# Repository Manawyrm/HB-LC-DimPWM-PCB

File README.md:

HomeBrew 16 channel dimmer
==========================

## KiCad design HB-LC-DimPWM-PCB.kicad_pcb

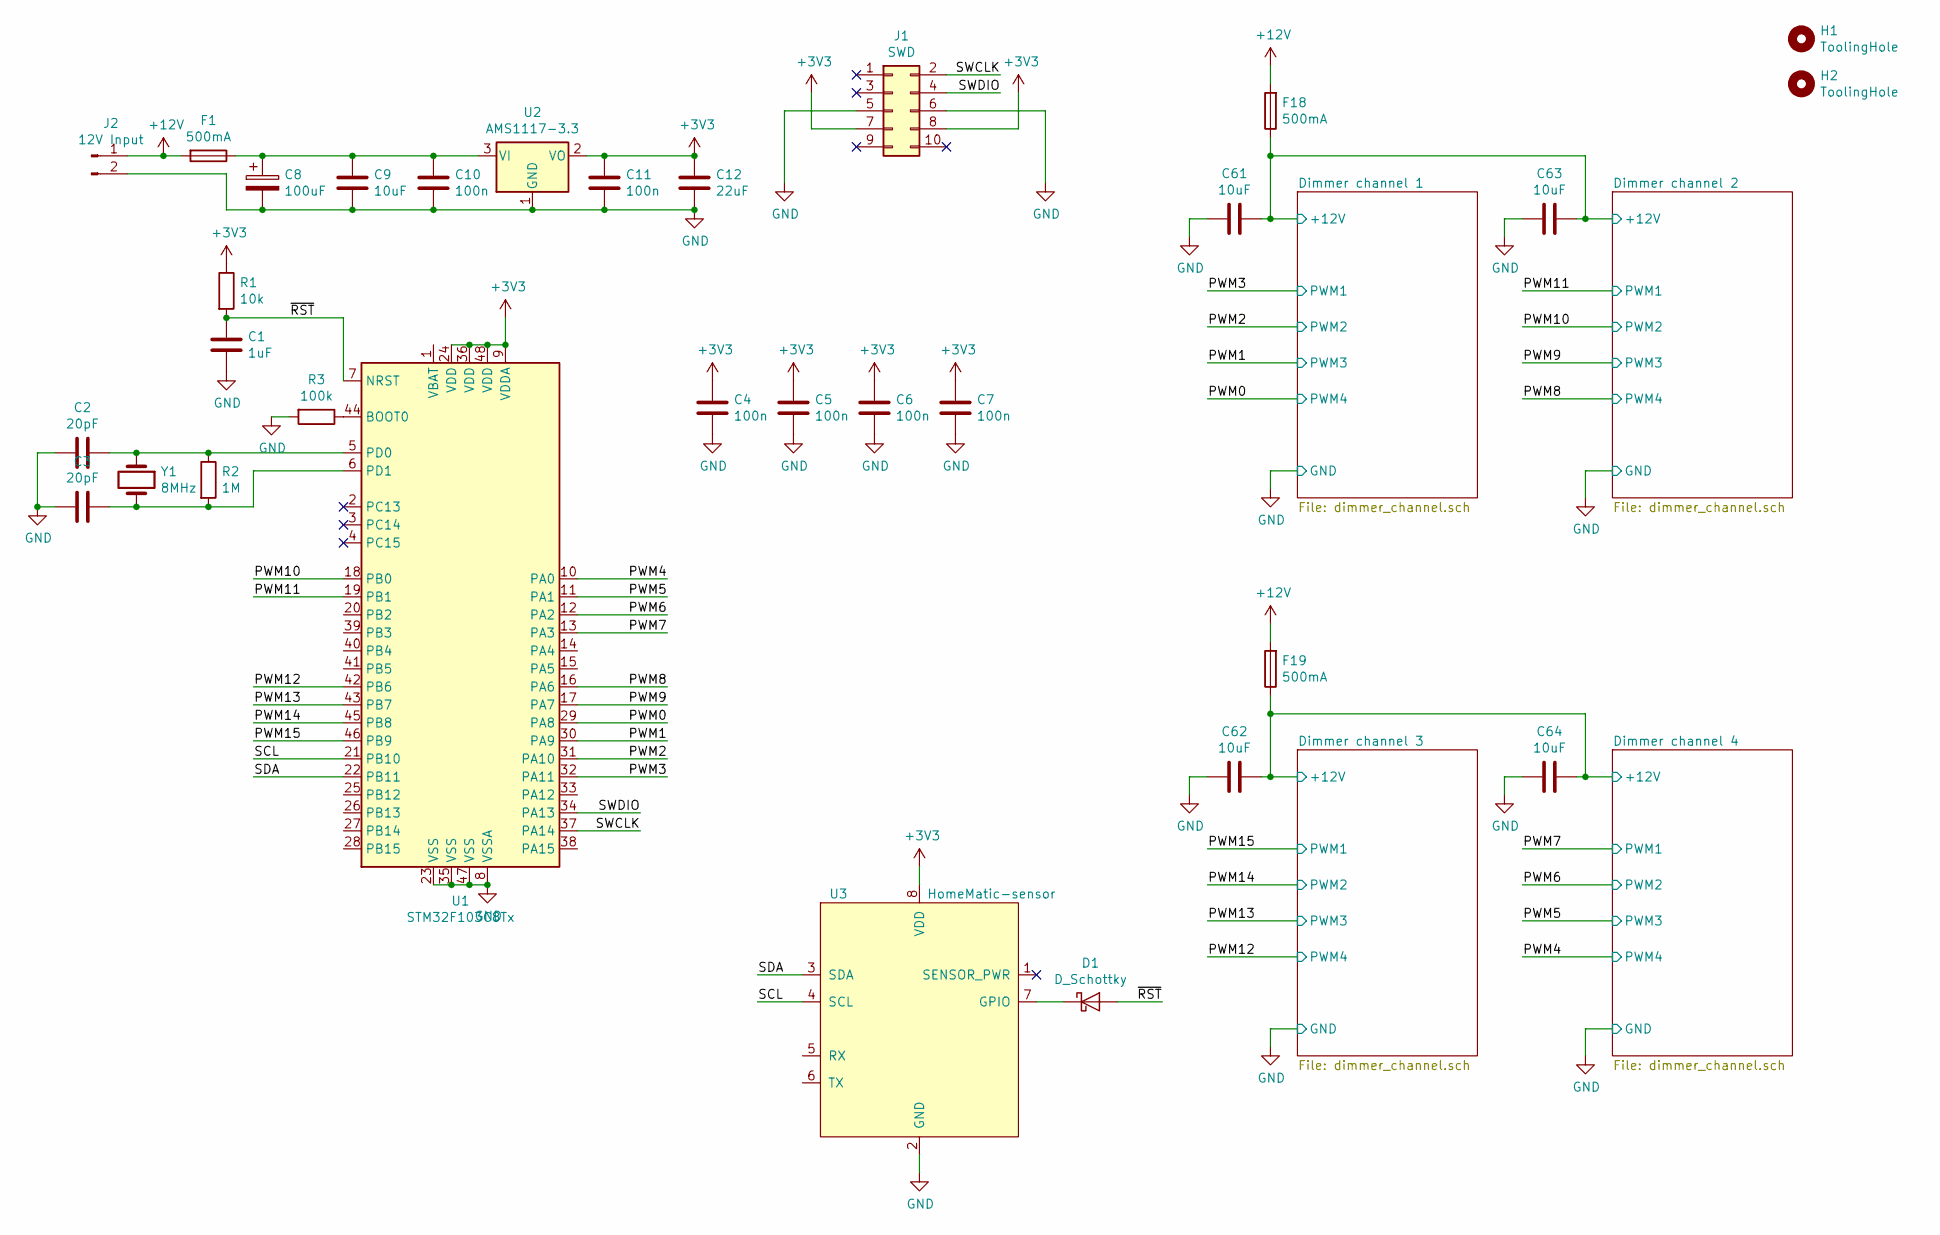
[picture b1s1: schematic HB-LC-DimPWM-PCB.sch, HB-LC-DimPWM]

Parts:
C1: 1uF; C_0402_1005Metric; LCSC C52923
C2, C3: 20pF; C_0402_1005Metric; LCSC C1554
C4, C5, C6, C7, C10, C11: 100n; C_0603_1608Metric; LCSC C14663
C8: 100uF; CP_Elec_8x6.7; LCSC C127967
C9: 10uF; C_0805_2012Metric; LCSC C15850
C12: 22uF; C_0603_1608Metric; LCSC C59461
C61, C62, C63, C64: 10uF; C_1206_3216Metric; LCSC C13585
D1: D_Schottky; D_SOD-123; LCSC C8598
F1, F18, F19: 500mA; Fuse_2512_6332Metric; LCSC C312001
H1, H2: ToolingHole; ToolingHole_JLCSMT
J1: SWD; IDC-Header_2x05_P2.54mm_Vertical
J2: 12V Input; Wago_714-162_1x02_P3.50mm_Horizontal
R1: 10k; R_0402_1005Metric; LCSC C25744
R2: 1M; R_0402_1005Metric; LCSC C26083
R3: 100k; R_0402_1005Metric; LCSC C25741
U1: STM32F103C8Tx; LQFP-48_7x7mm_P0.5mm; LCSC C8734
U2: AMS1117-3.3; SOT-223-3_TabPin2; LCSC C6186
U3: HomeMatic-sensor
Y1: 8MHz; Crystal_SMD_5032-2Pin_5.0x3.2mm; LCSC C115962

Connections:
+3V3: C4.1, C5.1, C6.1, C7.1, C11.1, C12.1, J1.7, J1.8, R1.1, U1.9 (VDDA), U1.24 (VDD), U1.36 (VDD), U1.48 (VDD), U2.2 (VO), U3.8 (VDD)
+12V: F1.2, F18.2, F19.2, J2.1
/Dimmer channel 1/+12V: C61.1, C63.1, F18.1; also elsewhere on the board
/Dimmer channel 3/+12V: C62.1, C64.1, F19.1; also elsewhere on the board
/PWM0: U1.29 (PA8); also elsewhere on the board
/PWM1: U1.30 (PA9); also elsewhere on the board
/PWM2: U1.31 (PA10); also elsewhere on the board
/PWM3: U1.32 (PA11); also elsewhere on the board
/PWM4: U1.10 (PA0); also elsewhere on the board
/PWM5: U1.11 (PA1); also elsewhere on the board
/PWM6: U1.12 (PA2); also elsewhere on the board
/PWM7: U1.13 (PA3); also elsewhere on the board
/PWM8: U1.16 (PA6); also elsewhere on the board
/PWM9: U1.17 (PA7); also elsewhere on the board
/PWM10: U1.18 (PB0); also elsewhere on the board
/PWM11: U1.19 (PB1); also elsewhere on the board
/PWM12: U1.42 (PB6); also elsewhere on the board
/PWM13: U1.43 (PB7); also elsewhere on the board
/PWM14: U1.45 (PB8); also elsewhere on the board
/PWM15: U1.46 (PB9); also elsewhere on the board
/SCL: U1.21 (PB10), U3.4 (SCL)
/SDA: U1.22 (PB11), U3.3 (SDA)
/SWCLK: J1.2, U1.37 (PA14)
/SWDIO: J1.4, U1.34 (PA13)
/~RST: C1.1, D1.2 (A), R1.2, U1.7 (NRST)
GND: C1.2, C2.1, C3.1, C4.2, C5.2, C6.2, C7.2, C8.2, C9.2, C10.2, C11.2, C12.2, C61.2, C62.2, C63.2, C64.2, J1.5, J1.6, J2.2, R3.2, U1.8 (VSSA), U1.23 (VSS), U1.35 (VSS), U1.47 (VSS), U2.1 (GND), U3.2 (GND); also elsewhere on the board
unnamed: C2.2, R2.1, U1.5 (PD0), Y1.1
unnamed: C3.2, R2.2, U1.6 (PD1), Y1.2
unnamed: C8.1, C9.1, C10.1, F1.1, U2.3 (VI)
unnamed: D1.1 (K), U3.7 (GPIO)
unnamed: R3.1, U1.44 (BOOT0)

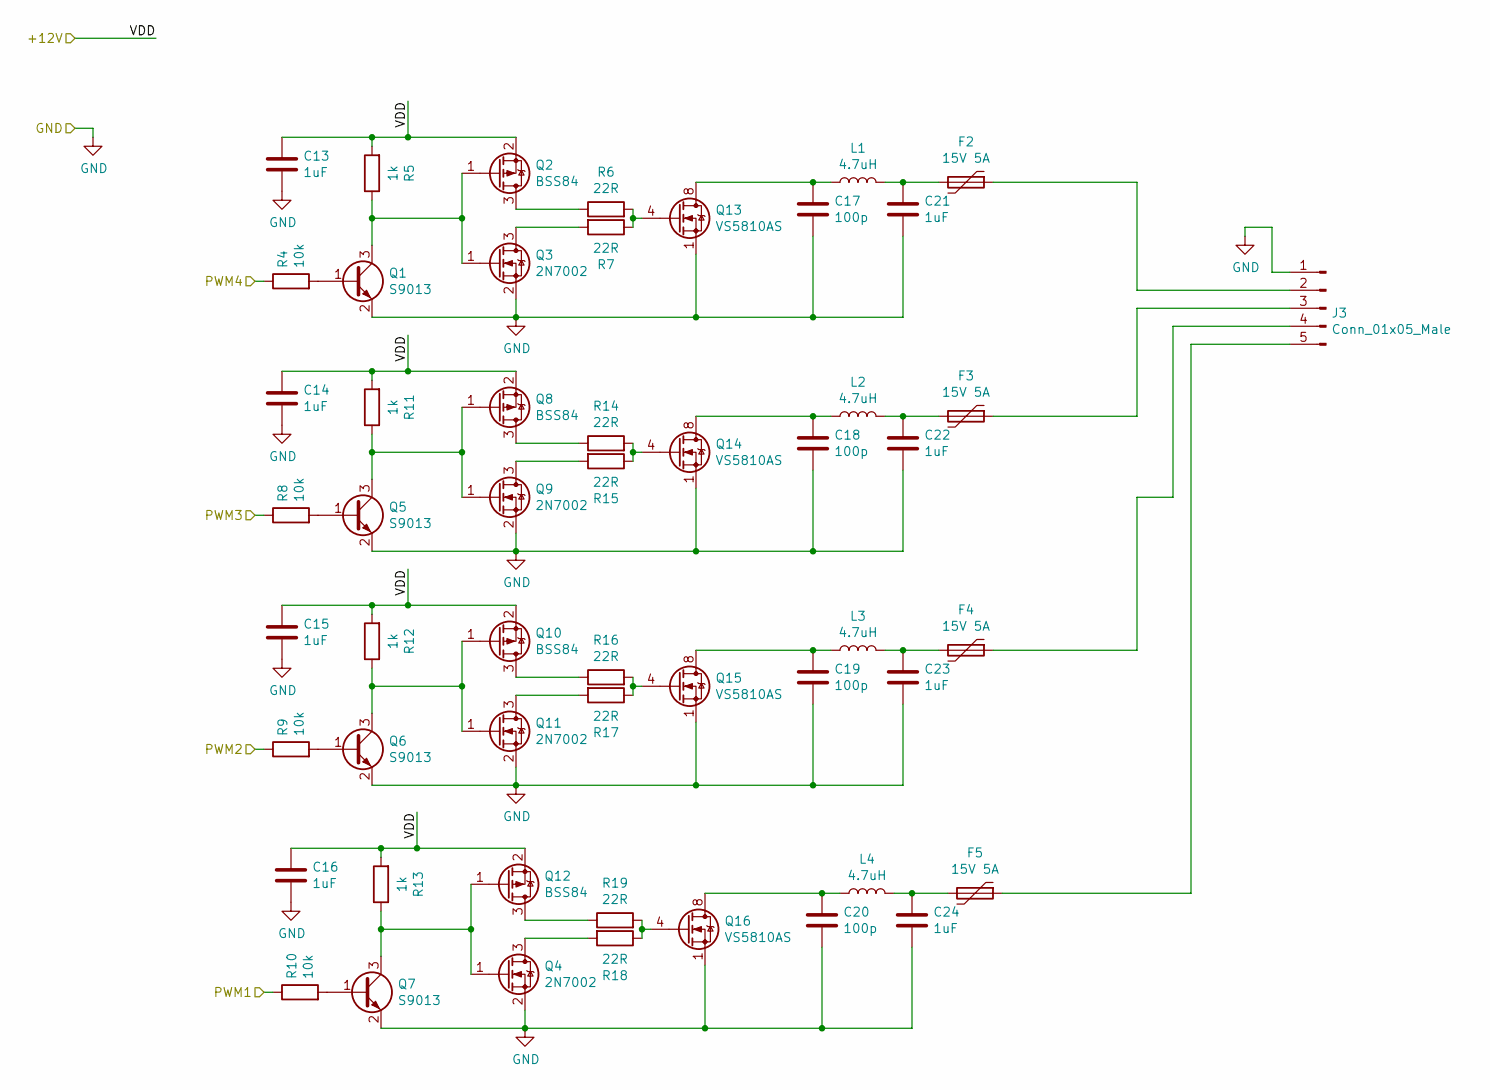
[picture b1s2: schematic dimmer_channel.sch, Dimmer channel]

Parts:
C13, C14, C15, C16: 1uF; C_0402_1005Metric; LCSC C52923
C17, C18, C19, C20: 100p; C_0805_2012Metric; LCSC C1790
C21, C22, C23: 1uF; C_1206_3216Metric; LCSC C1848
C24: 1uF; C_1206_3216Metric; LCSC C15849
F2, F3, F4, F5: 15V 5A; Fuse_2920_7451Metric; LCSC C207089
J3: Conn_01x05_Male; Wago_734-165_1x05_P3.50mm_Horizontal
L1, L2, L3, L4: 4.7uH; SMD-PIND-10.5x11.5x4_2.5x3.0; LCSC C183899
Q1, Q5, Q6, Q7: S9013; SOT-23; LCSC C6749
Q2, Q8, Q10, Q12: BSS84; SOT-23; LCSC C8492
Q3, Q4, Q9, Q11: 2N7002; SOT-23; LCSC C8545
Q13, Q14, Q15, Q16: VS5810AS; SOIC-8_3.9x4.9mm_P1.27mm; LCSC C427034
R4, R8, R9, R10: 10k; R_0402_1005Metric; LCSC C25744
R5, R11, R12, R13: 1k; R_0402_1005Metric; LCSC C11702
R6, R7, R14, R15, R16, R17, R18, R19: 22R; R_0603_1608Metric; LCSC C23345

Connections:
/Dimmer channel 1/+12V: C13.1, C14.1, C15.1, C16.1, Q2.2 (S), Q8.2 (S), Q10.2 (S), Q12.2 (S), R5.2, R11.2, R12.2, R13.2; also elsewhere on the board
/PWM0: R4.1; also elsewhere on the board
/PWM1: R8.1; also elsewhere on the board
/PWM2: R9.1; also elsewhere on the board
/PWM3: R10.1; also elsewhere on the board
GND: C13.2, C14.2, C15.2, C16.2, C17.2, C18.2, C19.2, C20.2, C21.2, C22.2, C23.2, C24.2, J3.1, Q1.2 (E), Q3.2 (S), Q4.2 (S), Q5.2 (E), Q6.2 (E), Q7.2 (E), Q9.2 (S), Q11.2 (S), Q13.1 (S), Q13.2 (S), Q13.3 (S), Q14.1 (S), Q14.2 (S), Q14.3 (S), Q15.1 (S), Q15.2 (S), Q15.3 (S), Q16.1 (S), Q16.2 (S), Q16.3 (S); also elsewhere on the board
unnamed: C17.1, L1.1, Q13.5 (D), Q13.6 (D), Q13.7 (D), Q13.8 (D)
unnamed: C18.1, L2.1, Q14.5 (D), Q14.6 (D), Q14.7 (D), Q14.8 (D)
unnamed: C19.1, L3.1, Q15.5 (D), Q15.6 (D), Q15.7 (D), Q15.8 (D)
unnamed: C20.1, L4.1, Q16.5 (D), Q16.6 (D), Q16.7 (D), Q16.8 (D)
unnamed: C21.1, F2.2, L1.2
unnamed: C22.1, F3.2, L2.2
unnamed: C23.1, F4.2, L3.2
unnamed: C24.1, F5.2, L4.2
unnamed: F2.1, J3.2
unnamed: F3.1, J3.3
unnamed: F4.1, J3.4
unnamed: F5.1, J3.5
unnamed: Q1.1 (B), R4.2
unnamed: Q1.3 (C), Q2.1 (G), Q3.1 (G), R5.1
unnamed: Q2.3 (D), R6.1
unnamed: Q3.3 (D), R7.2
unnamed: Q4.3 (D), R18.2
unnamed: Q5.1 (B), R8.2
unnamed: Q5.3 (C), Q8.1 (G), Q9.1 (G), R11.1
unnamed: Q6.1 (B), R9.2
unnamed: Q7.1 (B), R10.2
unnamed: Q8.3 (D), R14.1
unnamed: Q9.3 (D), R15.2
unnamed: Q6.3 (C), Q10.1 (G), Q11.1 (G), R12.1
unnamed: Q10.3 (D), R16.1
unnamed: Q11.3 (D), R17.2
unnamed: Q4.1 (G), Q7.3 (C), Q12.1 (G), R13.1
unnamed: Q12.3 (D), R19.1
unnamed: Q13.4 (G), R6.2, R7.1
unnamed: Q14.4 (G), R14.2, R15.1
unnamed: Q15.4 (G), R16.2, R17.1
unnamed: Q16.4 (G), R18.1, R19.2

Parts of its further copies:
C25, C26, C27, C28, C37, C38, C39, C40, C49, C50, C51, C52: 1uF; C_0402_1005Metric; LCSC C52923
C29, C30, C31, C32, C41, C42, C43, C44, C53, C54, C55, C56: 100p; C_0805_2012Metric; LCSC C1790
C33, C34, C35, C45, C46, C47, C57, C58, C59: 1uF; C_1206_3216Metric; LCSC C1848
C36, C48, C60: 1uF; C_1206_3216Metric; LCSC C15849
F6, F7, F8, F9, F10, F11, F12, F13, F14, F15, F16, F17: 15V 5A; Fuse_2920_7451Metric; LCSC C207089
J4, J5, J6: Conn_01x05_Male; Wago_734-165_1x05_P3.50mm_Horizontal
Q17, Q18, Q19, Q20, Q33, Q34, Q35, Q36, Q49, Q50, Q51, Q52: S9013; SOT-23; LCSC C6749
Q21, Q23, Q25, Q27, Q37, Q39, Q41, Q43, Q53, Q55, Q57, Q59: BSS84; SOT-23; LCSC C8492
Q22, Q24, Q26, Q28, Q38, Q40, Q42, Q44, Q54, Q56, Q58, Q60: 2N7002; SOT-23; LCSC C8545
Q29, Q30, Q31, Q32, Q45, Q46, Q47, Q48, Q61, Q62, Q63, Q64: VS5810AS; SOIC-8_3.9x4.9mm_P1.27mm; LCSC C427034
R20, R21, R22, R23, R36, R37, R38, R39, R52, R53, R54, R55: 10k; R_0402_1005Metric; LCSC C25744
R24, R25, R26, R27, R40, R41, R42, R43, R56, R57, R58, R59: 1k; R_0402_1005Metric; LCSC C11702
R28, R29, R30, R31, R32, R33, R34, R35, R44, R45, R46, R47, R48, R49, R50, R51, R60, R61, R62, R63, R64, R65, R66, R67: 22R; R_0603_1608Metric; LCSC C23345

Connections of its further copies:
/Dimmer channel 1/+12V: C25.1, C26.1, C27.1, C28.1, Q21.2 (S), Q23.2 (S), Q25.2 (S), Q27.2 (S), R24.2, R25.2, R26.2, R27.2; also elsewhere on the board
/Dimmer channel 3/+12V: C37.1, C38.1, C39.1, C40.1, C49.1, C50.1, C51.1, C52.1, Q37.2 (S), Q39.2 (S), Q41.2 (S), Q43.2 (S), Q53.2 (S), Q55.2 (S), Q57.2 (S), Q59.2 (S), R40.2, R41.2, R42.2, R43.2, R56.2, R57.2, R58.2, R59.2; also elsewhere on the board
/PWM4: R52.1; also elsewhere on the board
/PWM5: R53.1; also elsewhere on the board
/PWM6: R54.1; also elsewhere on the board
/PWM7: R55.1; also elsewhere on the board
/PWM8: R20.1; also elsewhere on the board
/PWM9: R21.1; also elsewhere on the board
/PWM10: R22.1; also elsewhere on the board
/PWM11: R23.1; also elsewhere on the board
/PWM12: R36.1; also elsewhere on the board
/PWM13: R37.1; also elsewhere on the board
/PWM14: R38.1; also elsewhere on the board
/PWM15: R39.1; also elsewhere on the board
GND: C25.2, C26.2, C27.2, C28.2, C29.2, C30.2, C31.2, C32.2, C33.2, C34.2, C35.2, C36.2, C37.2, C38.2, C39.2, C40.2, C41.2, C42.2, C43.2, C44.2, C45.2, C46.2, C47.2, C48.2, C49.2, C50.2, C51.2, C52.2, C53.2, C54.2, C55.2, C56.2, C57.2, C58.2, C59.2, C60.2, J4.1, J5.1, J6.1, Q17.2 (E), Q18.2 (E), Q19.2 (E), Q20.2 (E), Q22.2 (S), Q24.2 (S), Q26.2 (S), Q28.2 (S), Q29.1 (S), Q29.2 (S), Q29.3 (S), Q30.1 (S), Q30.2 (S), Q30.3 (S), Q31.1 (S), Q31.2 (S), Q31.3 (S), Q32.1 (S), Q32.2 (S), Q32.3 (S), Q33.2 (E), Q34.2 (E), Q35.2 (E), Q36.2 (E), Q38.2 (S), Q40.2 (S), Q42.2 (S), Q44.2 (S), Q45.1 (S), Q45.2 (S), Q45.3 (S), Q46.1 (S), Q46.2 (S), Q46.3 (S), Q47.1 (S), Q47.2 (S), Q47.3 (S), Q48.1 (S), Q48.2 (S), Q48.3 (S), Q49.2 (E), Q50.2 (E), Q51.2 (E), Q52.2 (E), Q54.2 (S), Q56.2 (S), Q58.2 (S), Q60.2 (S), Q61.1 (S), Q61.2 (S), Q61.3 (S), Q62.1 (S), Q62.2 (S), Q62.3 (S), Q63.1 (S), Q63.2 (S), Q63.3 (S), Q64.1 (S), Q64.2 (S), Q64.3 (S); also elsewhere on the board
unnamed 37: C29.1, Q29.5 (D), Q29.6 (D), Q29.7 (D), Q29.8 (D); also elsewhere on the board
unnamed 38: C30.1, Q30.5 (D), Q30.6 (D), Q30.7 (D), Q30.8 (D); also elsewhere on the board
unnamed 39: C31.1, Q31.5 (D), Q31.6 (D), Q31.7 (D), Q31.8 (D); also elsewhere on the board
unnamed 40: C32.1, Q32.5 (D), Q32.6 (D), Q32.7 (D), Q32.8 (D); also elsewhere on the board
unnamed 41: C33.1, F6.2; also elsewhere on the board
unnamed 42: C34.1, F7.2; also elsewhere on the board
unnamed 43: C35.1, F8.2; also elsewhere on the board
unnamed 44: C36.1, F9.2; also elsewhere on the board
unnamed 45: C41.1, Q45.5 (D), Q45.6 (D), Q45.7 (D), Q45.8 (D); also elsewhere on the board
unnamed 46: C42.1, Q46.5 (D), Q46.6 (D), Q46.7 (D), Q46.8 (D); also elsewhere on the board
unnamed 47: C43.1, Q47.5 (D), Q47.6 (D), Q47.7 (D), Q47.8 (D); also elsewhere on the board
unnamed 48: C44.1, Q48.5 (D), Q48.6 (D), Q48.7 (D), Q48.8 (D); also elsewhere on the board
unnamed 49: C45.1, F10.2; also elsewhere on the board
unnamed 50: C46.1, F11.2; also elsewhere on the board
unnamed 51: C47.1, F12.2; also elsewhere on the board
unnamed 52: C48.1, F13.2; also elsewhere on the board
unnamed 53: C53.1, Q61.5 (D), Q61.6 (D), Q61.7 (D), Q61.8 (D); also elsewhere on the board
unnamed 54: C54.1, Q62.5 (D), Q62.6 (D), Q62.7 (D), Q62.8 (D); also elsewhere on the board
unnamed 55: C55.1, Q63.5 (D), Q63.6 (D), Q63.7 (D), Q63.8 (D); also elsewhere on the board
unnamed 56: C56.1, Q64.5 (D), Q64.6 (D), Q64.7 (D), Q64.8 (D); also elsewhere on the board
unnamed 57: C57.1, F14.2; also elsewhere on the board
unnamed 58: C58.1, F15.2; also elsewhere on the board
unnamed 59: C59.1, F16.2; also elsewhere on the board
unnamed 60: C60.1, F17.2; also elsewhere on the board
unnamed: F6.1, J4.2
unnamed: F7.1, J4.3
unnamed: F8.1, J4.4
unnamed: F9.1, J4.5
unnamed: F10.1, J5.2
unnamed: F11.1, J5.3
unnamed: F12.1, J5.4
unnamed: F13.1, J5.5
unnamed: F14.1, J6.2
unnamed: F15.1, J6.3
unnamed: F16.1, J6.4
unnamed: F17.1, J6.5
unnamed: Q17.1 (B), R20.2
unnamed: Q17.3 (C), Q21.1 (G), Q22.1 (G), R24.1
unnamed: Q18.1 (B), R21.2
unnamed: Q18.3 (C), Q23.1 (G), Q24.1 (G), R25.1
unnamed: Q19.1 (B), R22.2
unnamed: Q19.3 (C), Q25.1 (G), Q26.1 (G), R26.1
unnamed: Q20.1 (B), R23.2
unnamed: Q20.3 (C), Q27.1 (G), Q28.1 (G), R27.1
unnamed: Q21.3 (D), R28.1
unnamed: Q22.3 (D), R29.2
unnamed: Q23.3 (D), R30.1
unnamed: Q24.3 (D), R31.2
unnamed: Q25.3 (D), R32.1
unnamed: Q26.3 (D), R33.2
unnamed: Q27.3 (D), R34.1
unnamed: Q28.3 (D), R35.2
unnamed: Q29.4 (G), R28.2, R29.1
unnamed: Q30.4 (G), R30.2, R31.1
unnamed: Q31.4 (G), R32.2, R33.1
unnamed: Q32.4 (G), R34.2, R35.1
unnamed: Q33.1 (B), R36.2
unnamed: Q33.3 (C), Q37.1 (G), Q38.1 (G), R40.1
unnamed: Q34.1 (B), R37.2
unnamed: Q34.3 (C), Q39.1 (G), Q40.1 (G), R41.1
unnamed: Q35.1 (B), R38.2
unnamed: Q35.3 (C), Q41.1 (G), Q42.1 (G), R42.1
unnamed: Q36.1 (B), R39.2
unnamed: Q36.3 (C), Q43.1 (G), Q44.1 (G), R43.1
unnamed: Q37.3 (D), R44.1
unnamed: Q38.3 (D), R45.2
unnamed: Q39.3 (D), R46.1
unnamed: Q40.3 (D), R47.2
unnamed: Q41.3 (D), R48.1
unnamed: Q42.3 (D), R49.2
unnamed: Q43.3 (D), R50.1
unnamed: Q44.3 (D), R51.2
unnamed: Q45.4 (G), R44.2, R45.1
unnamed: Q46.4 (G), R46.2, R47.1
unnamed: Q47.4 (G), R48.2, R49.1
unnamed: Q48.4 (G), R50.2, R51.1
unnamed: Q49.1 (B), R52.2
unnamed: Q49.3 (C), Q53.1 (G), Q54.1 (G), R56.1
unnamed: Q50.1 (B), R53.2
unnamed: Q50.3 (C), Q55.1 (G), Q56.1 (G), R57.1
unnamed: Q51.1 (B), R54.2
unnamed: Q51.3 (C), Q57.1 (G), Q58.1 (G), R58.1
unnamed: Q52.1 (B), R55.2
unnamed: Q52.3 (C), Q59.1 (G), Q60.1 (G), R59.1
unnamed: Q53.3 (D), R60.1
unnamed: Q54.3 (D), R61.2
unnamed: Q55.3 (D), R62.1
unnamed: Q56.3 (D), R63.2
unnamed: Q57.3 (D), R64.1
unnamed: Q58.3 (D), R65.2
unnamed: Q59.3 (D), R66.1
unnamed: Q60.3 (D), R67.2
unnamed: Q61.4 (G), R60.2, R61.1
unnamed: Q62.4 (G), R62.2, R63.1
unnamed: Q63.4 (G), R64.2, R65.1
unnamed: Q64.4 (G), R66.2, R67.1

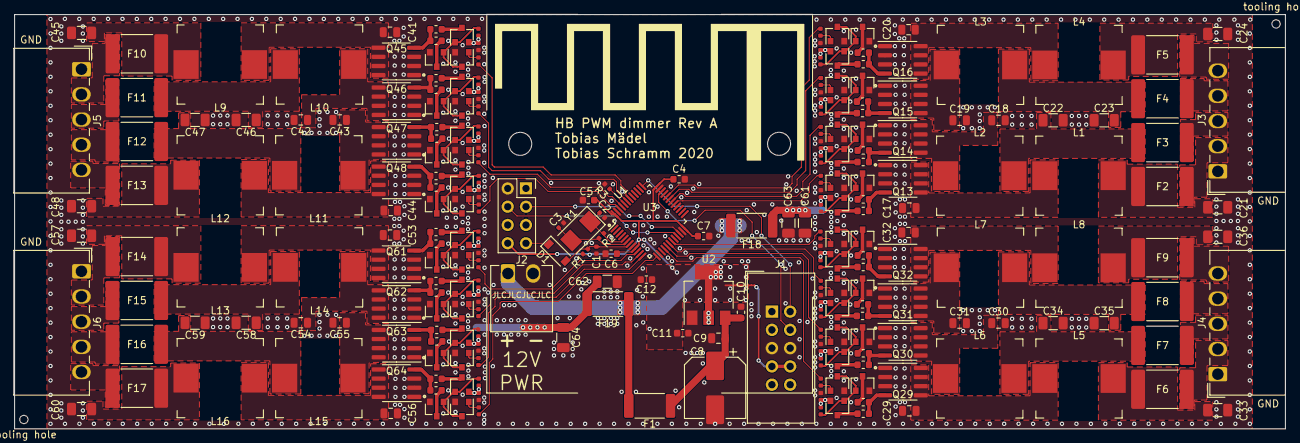
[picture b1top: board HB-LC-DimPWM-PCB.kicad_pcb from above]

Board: 2 copper layers, 176.7 x 57.6 mm, 243 parts (0 on the bottom side), 159 nets.

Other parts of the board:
L5, L6, L7, L8, L9, L10, L11, L12, L13, L14, L15, L16: 3.3uH; SMD-PIND-10.5x11.5x4_2.5x3.0

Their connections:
unnamed 37: L5.1; also elsewhere on the board
unnamed 38: L6.1; also elsewhere on the board
unnamed 39: L7.1; also elsewhere on the board
unnamed 40: L8.1; also elsewhere on the board
unnamed 41: L5.2; also elsewhere on the board
unnamed 42: L6.2; also elsewhere on the board
unnamed 43: L7.2; also elsewhere on the board
unnamed 44: L8.2; also elsewhere on the board
unnamed 45: L9.1; also elsewhere on the board
unnamed 46: L10.1; also elsewhere on the board
unnamed 47: L11.1; also elsewhere on the board
unnamed 48: L12.1; also elsewhere on the board
unnamed 49: L9.2; also elsewhere on the board
unnamed 50: L10.2; also elsewhere on the board
unnamed 51: L11.2; also elsewhere on the board
unnamed 52: L12.2; also elsewhere on the board
unnamed 53: L13.1; also elsewhere on the board
unnamed 54: L14.1; also elsewhere on the board
unnamed 55: L15.1; also elsewhere on the board
unnamed 56: L16.1; also elsewhere on the board
unnamed 57: L13.2; also elsewhere on the board
unnamed 58: L14.2; also elsewhere on the board
unnamed 59: L15.2; also elsewhere on the board
unnamed 60: L16.2; also elsewhere on the board

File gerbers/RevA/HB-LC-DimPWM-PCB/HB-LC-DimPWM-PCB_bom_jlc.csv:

"Comment","Designator","Footprint","LCSC Part #"
"1uF","C1,C13,C14,C15,C16,C25,C26,C27,C28,C37,C38,C39,C40,C49,C50,C51,C52","C_0402_1005Metric","C52923"
"20pF","C3,C2","C_0402_1005Metric","C1554"
"100uF","C8","CP_Elec_8x6.7","C127967"
"10uF","C9","C_0805_2012Metric","C15850"
"100n","C10,C11,C7,C6,C5,C4","C_0603_1608Metric","C14663"
"22uF","C12","C_0603_1608Metric","C59461"
"100p","C17,C18,C19,C20,C29,C30,C31,C32,C41,C42,C43,C44,C53,C54,C55,C56","C_0805_2012Metric","C1790"
"1uF","C21,C22,C23,C24,C33,C34,C35,C36,C45,C46,C47,C48,C57,C58,C59,C60","C_1206_3216Metric","C1848"
"10uF","C64,C62,C61,C63","C_1206_3216Metric","C13585"
"D_Schottky","D1","D_SOD-123","C8598"
"500mA","F1,F18,F19","Fuse_2512_6332Metric","C312001"
"15V 5A","F2,F3,F4,F5,F6,F7,F8,F9,F10,F11,F12,F13,F14,F15,F16,F17","Fuse_2920_7451Metric","C207089"
"4.7uH","L1,L2,L4,L3,L5,L6,L8,L7,L9,L10,L12,L11,L13,L14,L16,L15","SMD-PIND-10.5x11.5x4_2.5x3.0","C183899"
"S9013","Q1,Q5,Q6,Q7,Q17,Q18,Q19,Q20,Q33,Q34,Q35,Q36,Q49,Q50,Q51,Q52","SOT-23","C6749"
"BSS84","Q2,Q8,Q10,Q12,Q21,Q23,Q25,Q27,Q37,Q39,Q41,Q43,Q53,Q55,Q57,Q59","SOT-23","C8492"
"2N7002","Q3,Q9,Q11,Q4,Q22,Q24,Q26,Q28,Q38,Q40,Q42,Q44,Q54,Q56,Q58,Q60","SOT-23","C8545"
"VS5810AS","Q14,Q15,Q16,Q13,Q30,Q31,Q32,Q29,Q46,Q47,Q48,Q45,Q62,Q63,Q64,Q61","SOIC-8_3.9x4.9mm_P1.27mm","C427034"
"10k","R1,R4,R9,R10,R8,R20,R22,R23,R21,R36,R38,R39,R37,R52,R54,R55,R53","R_0402_1005Metric","C25744"
"1M","R2","R_0402_1005Metric","C26083"
"100k","R3","R_0402_1005Metric","C25741"
"1k","R5,R11,R12,R13,R24,R25,R26,R27,R40,R41,R42,R43,R56,R57,R58,R59","R_0402_1005Metric","C11702"
"22R","R6,R15,R14,R17,R16,R18,R19,R7,R28,R31,R30,R33,R32,R35,R34,R29,R44,R47,R46,R49,R48,R51,R50,R45,R60,R63,R62,R65,R64,R67,R66,R61","R_0603_1608Metric","C23345"
"STM32F103C8Tx","U1","LQFP-48_7x7mm_P0.5mm","C8734"
"AMS1117-3.3","U2","SOT-223-3_TabPin2","C6186"
"8MHz","Y1","Crystal_SMD_5032-2Pin_5.0x3.2mm","C115962"

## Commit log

2020-03-29 Add alternate gate driver setup
2020-04-03 Layout one dimmer channel
2020-04-03 Optimize channel layout
2020-04-03 Add more space for GND vias below dimmer FETs
2020-04-03 Add full layout as PoC
2020-04-03 Update sensor model
2020-04-04 Add gitignore
2020-04-04 Move dimmer channels to subsheet
2020-04-04 Use hierarchical sheet for dimmer channels
2020-04-04 Mark Sunlord inductor as SMD part
2020-04-04 Finish layout of first four dimmer channels
2020-04-04 Reduce solder mask clearance to 0
2020-04-04 First eight channels finished
2020-04-04 All 16 channels layouted
2020-04-04 Replace 5.08 mm pitch headers by 3.5 mm pitch
2020-04-04 Add wago 714 connectors
2020-04-04 Layout board
2020-04-04 Add wago 734 3d models
2020-04-05 Internal kicad reordering
    No idea why that happened
2020-04-05 Add additional bypassing
    Add 4x 10uF to gate driver supplies
2020-04-05 Add tons of manual via stitching
2020-04-05 Add pin 1 markers
2020-04-05 Remove vias too close to one another for safe drilling
2020-04-05 Mark GND pin on lamp connectors
2020-04-05 Add revision indicator
2020-04-05 Add PWM channel designators
2020-04-05 Include HB sensor lib via relative path
2020-04-05 Add metadata to schematic
2020-04-05 Remove rescue lib
2020-04-05 Add tooling holes
2020-04-05 Fix GND marking orientation
2020-04-05 Change inductor to 4.7uH for JLC assembly
2020-04-05 Add path configuration for gerber output
2020-04-05 Add gerbers, PDF schematics and render image for RevA
2020-04-05 Fix orientation of polymer cap for JLC
2020-04-05 Add interactive HTML bom
2020-04-06 Fix 1206 component with 0603 LCSC part number (1uF cap)
2020-04-06 Add new fixed production data for JLC
2020-04-07 Add missing 3d models
2020-04-07 Fix possible collision between sensor module and F19
    Height of F19 is 2.6 mm, could collide with ISP header if not centered properly
2020-04-07 Set default via drill hole size to .3 mm
2020-04-07 Resize fuse 3d models for more realistic 3d view
2020-04-07 Allign dimmer channels on schematic
2020-04-07 Use 3d inductor model closer to actual inductor used
2020-04-15 Move designator C62 to unobstructed place
2020-04-22 Remove duplicate LCSC part number
